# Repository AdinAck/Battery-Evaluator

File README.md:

# Battery-Evaluator
A comprehensive battery evaluator board for running simple tests and measurements, or creating a battery profile for accurately predicting charge level from voltage.

## Electrical Characteristics
- 0-5v battery (single cell)
- 0-1000mA programable constant current draw
- Do not reverse polarity of battery, the board will die
- While you *can* plug in a battery before USB is plugged in... you shouldn't

## Software Features
- Graph the measured and predicted battery voltage with respect to mAh consumed
- Measure ESR
- Measure mWh consumed
- Monitor temperature of FETs and resistors

## To Be Implemented
- More battery chemistries
- [Op-Amp oscillation fix](https://github.com/AdinAck/Battery-Evaluator/issues/1)
- Combine multiple constant current tests to make the ultimate battery profile
- Generate voltage, current -> percent charge function

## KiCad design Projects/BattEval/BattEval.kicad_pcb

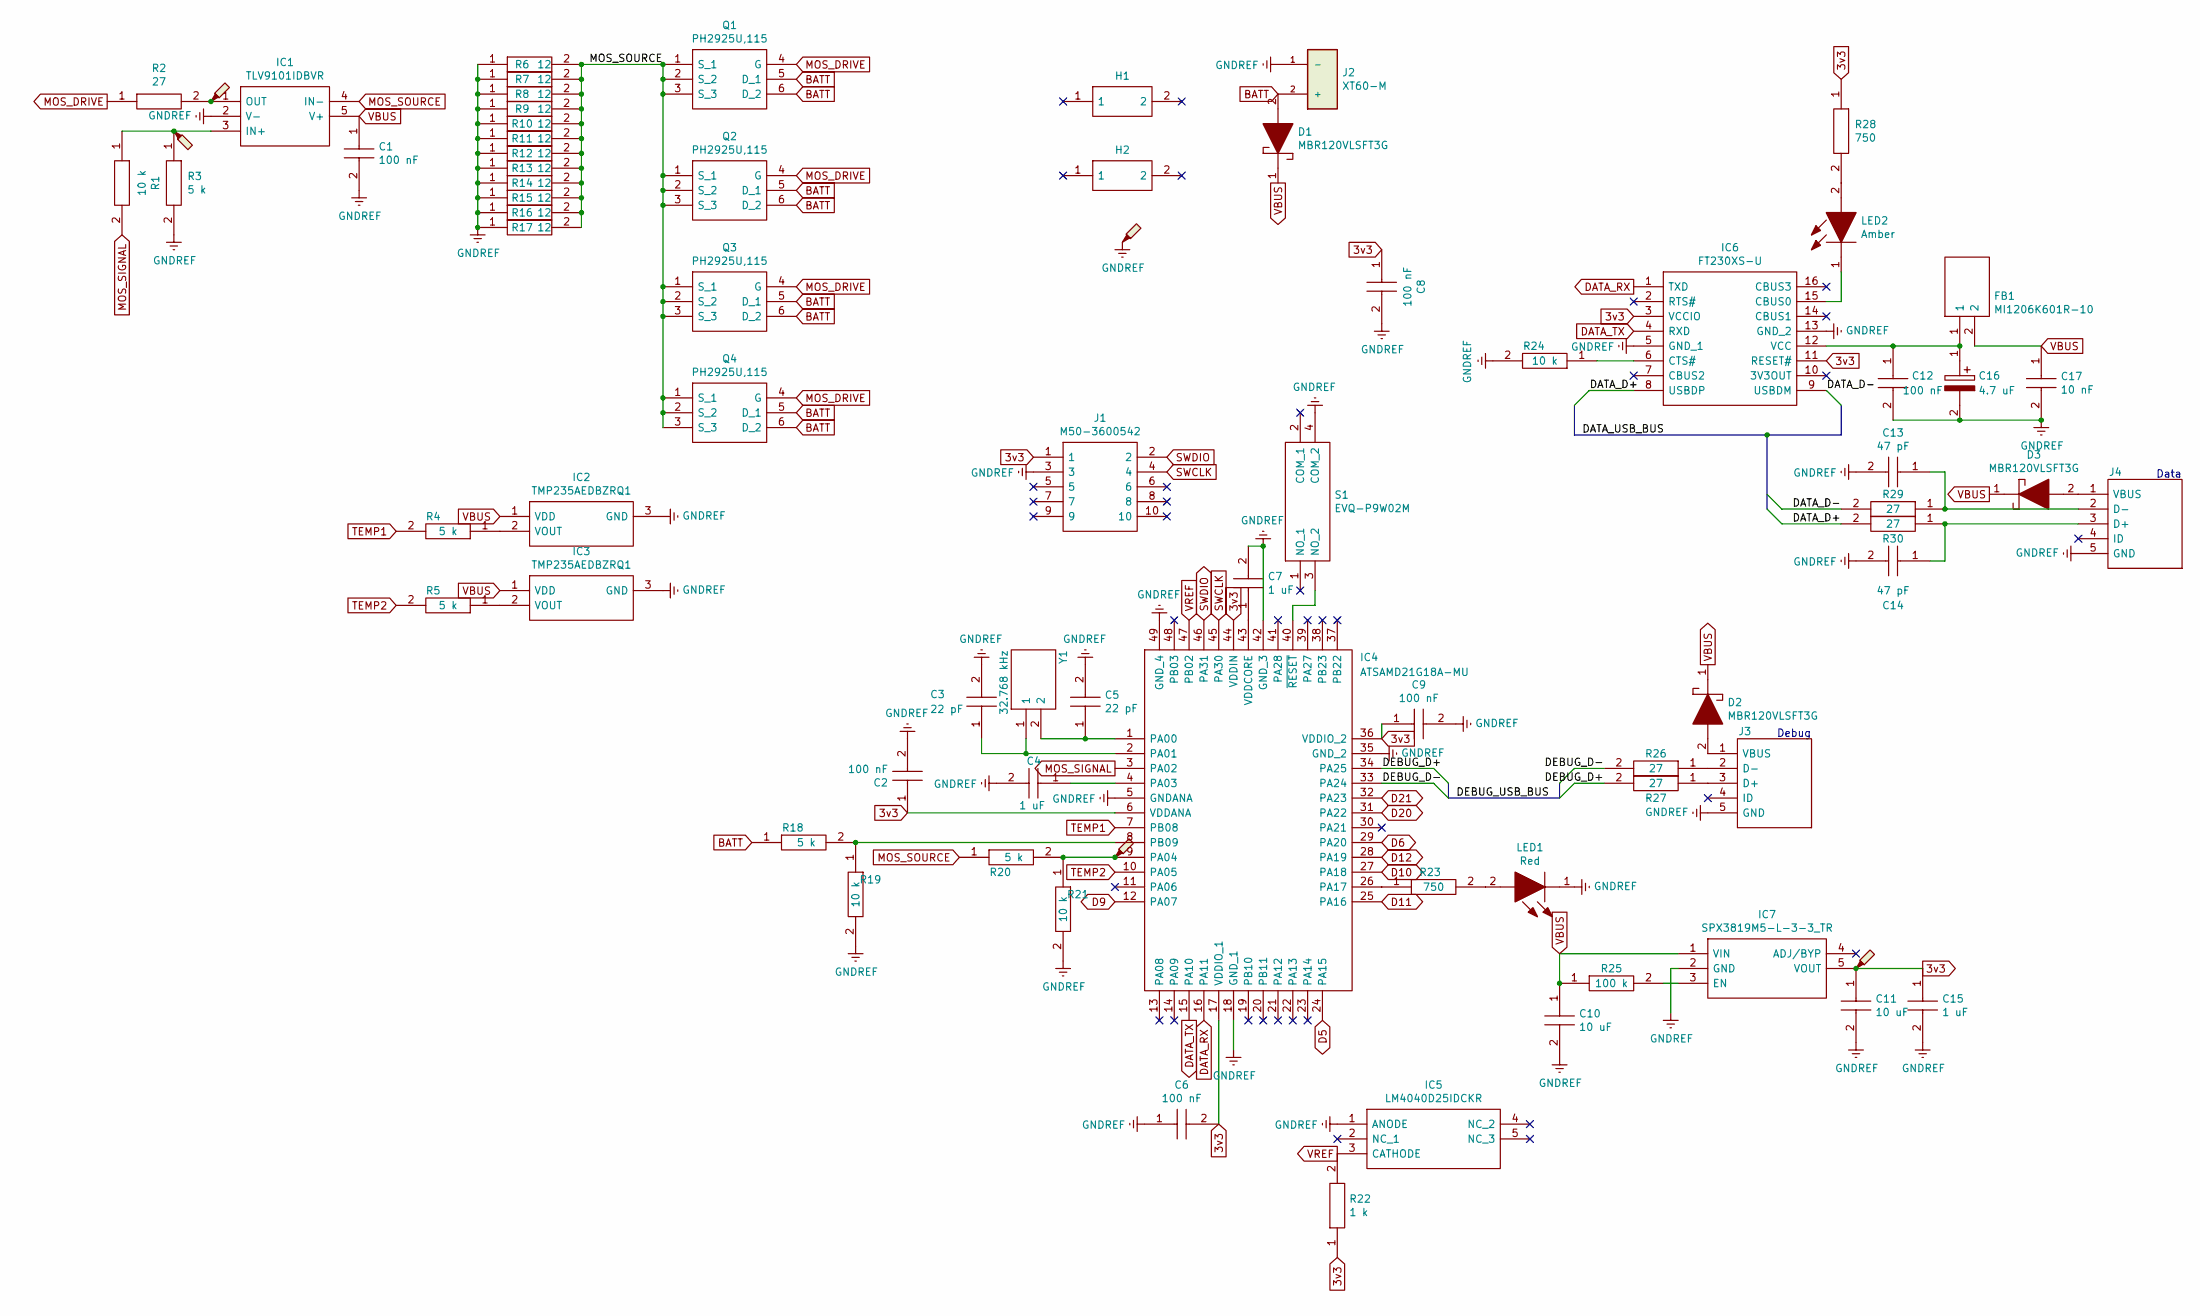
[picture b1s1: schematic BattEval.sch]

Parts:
C1, C2, C6, C8, C9, C12: 06033C104KAT2A; CAPC1608X90N; Mouser Part Number 581-06033C104KAT2A
C3, C5: 06035A220JAT4A; CAPC1608X90N; Mouser Part Number 581-06035A220JAT4A
C4, C7, C15: 0603ZC105KAT2A; CAPC1608X90N; Mouser Part Number 581-0603ZC105KAT2A
C10, C11: 0603ZD106KAT4A; CAPC1608X90N; Mouser Part Number 581-0603ZD106KAT4A
C13, C14: 06033C470KAT2A; CAPC1608X90N; Mouser Part Number 581-06033C470KAT2A
C16: TAJA475K010RNJV; CAPPM3216X180N; Mouser Part Number 581-TAJA475K010RNJV
C17: 0603ZC103KAT2A; CAPC1608X90N; Mouser Part Number 581-0603ZC103K
D1, D2, D3: MBR120VLSFT3G; SODFL3616X98N; Mouser Part Number 863-MBR120VLSFT3G
FB1: MI1206K601R-10; BEADC3216X130N; Mouser Part Number N/A
H1, H2: 960-23-12-D-AB-0; 9602312DAB0; Mouser Part Number 567-960-23-12-D-AB-0
IC1: TLV9101IDBVR; SOT95P280X145-5N; Mouser Part Number 595-TLV9101IDBVR
IC2, IC3: TMP235AEDBZRQ1; SOT95P237X112-3N; Mouser Part Number 595-TMP235AEDBZRQ1
IC4: ATSAMD21G18A-MU; QFN50P700X700X90-49N-D; Mouser Part Number 556-ATSAMD21G18A-MU
IC5: LM4040D25IDCKR; SOT65P210X110-5N; Mouser Part Number 595-LM4040D25IDCKR
IC6: FT230XS-U; SOP64P599X175-16N; Mouser Part Number 895-FT230XS-U
IC7: SPX3819M5-L-3-3_TR; SOT95P280X145-5N; Mouser Part Number 701-SPX3819M5-L-33TR
J1: M50-3600542; M503600542; Mouser Part Number 855-M50-3600542
J2: XT60-M; AMASS_XT60-M; PARTREV 1.2
J3, J4: 47346-0001; Mouser Part Number 538-47346-0001
LED1: APT1608LSECK_J3-PRV; APT1608CGCK; Mouser Part Number 604-APT1608LSECKJ3RV
LED2: 150060AS75000; LEDC1608X80N; Mouser Part Number 710-150060AS75000
Q1, Q2, Q3, Q4: PH2925U,115; PSMN5R660YLX; Mouser Part Number 771-PH2925U115
R1, R19, R21, R24: ERJ-S02F1002X; RESC1005X40N; Mouser Part Number 667-ERJ-S02F1002X
R2, R26, R27, R29, R30: ERJ2RKD27R0X; RESC1005X40N; Mouser Part Number 667-ERJ-2RKD27R0X
R3, R4, R5, R18, R20: RC0402FR-075KL; RESC1005X40N; Mouser Part Number 603-RC0402FR-075KL
R6, R7, R8, R9, R10, R11, R12, R13, R14, R15, R16, R17: CRGP2512F12R; RESC6432X65N; Mouser Part Number 279-CRGP2512F12R
R22: ERJ-U02F1001X; RESC1005X40N; Mouser Part Number 667-ERJ-U02F1001X
R23, R28: ERJ-2RKF7500X; RESC1005X40N; Mouser Part Number 667-ERJ-2RKF7500X
R25: ERJ-U02F1003X; RESC1005X40N; Mouser Part Number 667-ERJ-U02F1003X
S1: EVQ-P9W02M; EVQP9W02M; Mouser Part Number 667-EVQ-P9W02M
TP1, TP2, TP3, TP4, TP5: TestPoint_Probe; Standard_Probe_Point
Y1: CM7V-T1A-32.768kHz-6pF-20PPM-TA-QC; CM7VT1A32768kHz6pF20PPMTAQC; Mouser Part Number 428-201843-MG01

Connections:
3v3: C2.1, C6.2, C8.1, C9.1, C11.1, C15.1, IC4.6 (VDDANA), IC4.17 (VDDIO_1), IC4.36 (VDDIO_2), IC4.44 (VDDIN), IC6.3 (VCCIO), IC6.11 (RESET#), IC7.5 (VOUT), J1.1, R22.1, R28.1, TP5.1
/DATA_D+: IC6.8 (USBDP), R30.2
/DATA_D-: IC6.9 (USBDM), R29.2
/DEBUG_D+: IC4.34 (PA25), R27.2
/DEBUG_D-: IC4.33 (PA24), R26.2
BATT: D1.2, J2.2 (+), Q1.5 (D_1), Q1.6 (D_2), Q2.5 (D_1), Q2.6 (D_2), Q3.5 (D_1), Q3.6 (D_2), Q4.5 (D_1), Q4.6 (D_2), R18.1
D5: IC4.24 (PA15)
D6: IC4.29 (PA20)
D9: IC4.12 (PA07)
D10: IC4.27 (PA18)
D11: IC4.25 (PA16)
D12: IC4.28 (PA19)
D20: IC4.31 (PA22)
D21: IC4.32 (PA23)
DATA_RX: IC4.16 (PA11), IC6.1 (TXD)
DATA_TX: IC4.15 (PA10), IC6.4 (RXD)
GNDREF: C1.2, C2.2, C3.2, C4.2, C5.2, C6.1, C7.2, C8.2, C9.2, C10.2, C11.2, C12.2, C13.2, C14.2, C15.2, C16.2, C17.2, IC1.2 (V-), IC2.3 (GND), IC3.3 (GND), IC4.5 (GNDANA), IC4.18 (GND_1), IC4.35 (GND_2), IC4.42 (GND_3), IC4.49 (GND_4), IC5.1 (ANODE), IC6.5 (GND_1), IC6.13 (GND_2), IC7.2 (GND), J1.3, J2.1 (-), J3.5 (GND), J4.5 (GND), LED1.1, R3.2, R6.1, R7.1, R8.1, R9.1, R10.1, R11.1, R12.1, R13.1, R14.1, R15.1, R16.1, R17.1, R19.2, R21.2, R24.2, S1.4 (COM_2), TP4.1
MOS_DRIVE: Q1.4 (G), Q2.4 (G), Q3.4 (G), Q4.4 (G), R2.1
MOS_SIGNAL: IC4.3 (PA02), R1.2
MOS_SOURCE: IC1.4 (IN-), Q1.1 (S_1), Q1.2 (S_2), Q1.3 (S_3), Q2.1 (S_1), Q2.2 (S_2), Q2.3 (S_3), Q3.1 (S_1), Q3.2 (S_2), Q3.3 (S_3), Q4.1 (S_1), Q4.2 (S_2), Q4.3 (S_3), R6.2, R7.2, R8.2, R9.2, R10.2, R11.2, R12.2, R13.2, R14.2, R15.2, R16.2, R17.2, R20.1
unnamed: C3.1, IC4.2 (PA01), Y1.1
unnamed: C4.1, IC4.4 (PA03)
unnamed: C5.1, IC4.1 (PA00), Y1.2
unnamed: C7.1, IC4.43 (VDDCORE)
unnamed: C12.1, C16.1, FB1.1, IC6.12 (VCC)
unnamed: C13.1, J4.2 (D-), R29.1
unnamed: C14.1, J4.3 (D+), R30.1
unnamed: D2.2, J3.1 (VBUS)
unnamed: D3.2, J4.1 (VBUS)
unnamed: IC1.1 (OUT), R2.2, TP2.1
unnamed: IC1.3 (IN+), R1.1, R3.1, TP1.1
unnamed: IC2.2 (VOUT), R4.1
unnamed: IC3.2 (VOUT), R5.1
unnamed: IC4.8 (PB09), R18.2, R19.1
unnamed: IC4.9 (PA04), R20.2, R21.1, TP3.1
unnamed: IC4.26 (PA17), R23.1
unnamed: IC4.40 (~RESET), S1.3 (NO_2)
unnamed: IC6.6 (CTS#), R24.1
unnamed: IC6.15 (CBUS0), LED2.1
unnamed: IC7.3 (EN), R25.2
unnamed: J3.2 (D-), R26.1
unnamed: J3.3 (D+), R27.1
unnamed: LED1.2, R23.2
unnamed: LED2.2, R28.2
SWCLK: IC4.45 (PA30), J1.4
SWDIO: IC4.46 (PA31), J1.2
TEMP1: IC4.7 (PB08), R4.2
TEMP2: IC4.10 (PA05), R5.2
VBUS: C1.1, C10.1, C17.1, D1.1, D2.1, D3.1, FB1.2, IC1.5 (V+), IC2.1 (VDD), IC3.1 (VDD), IC7.1 (VIN), R25.1
VREF: IC4.47 (PB02), IC5.3 (CATHODE), R22.2

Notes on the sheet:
Debug
Data

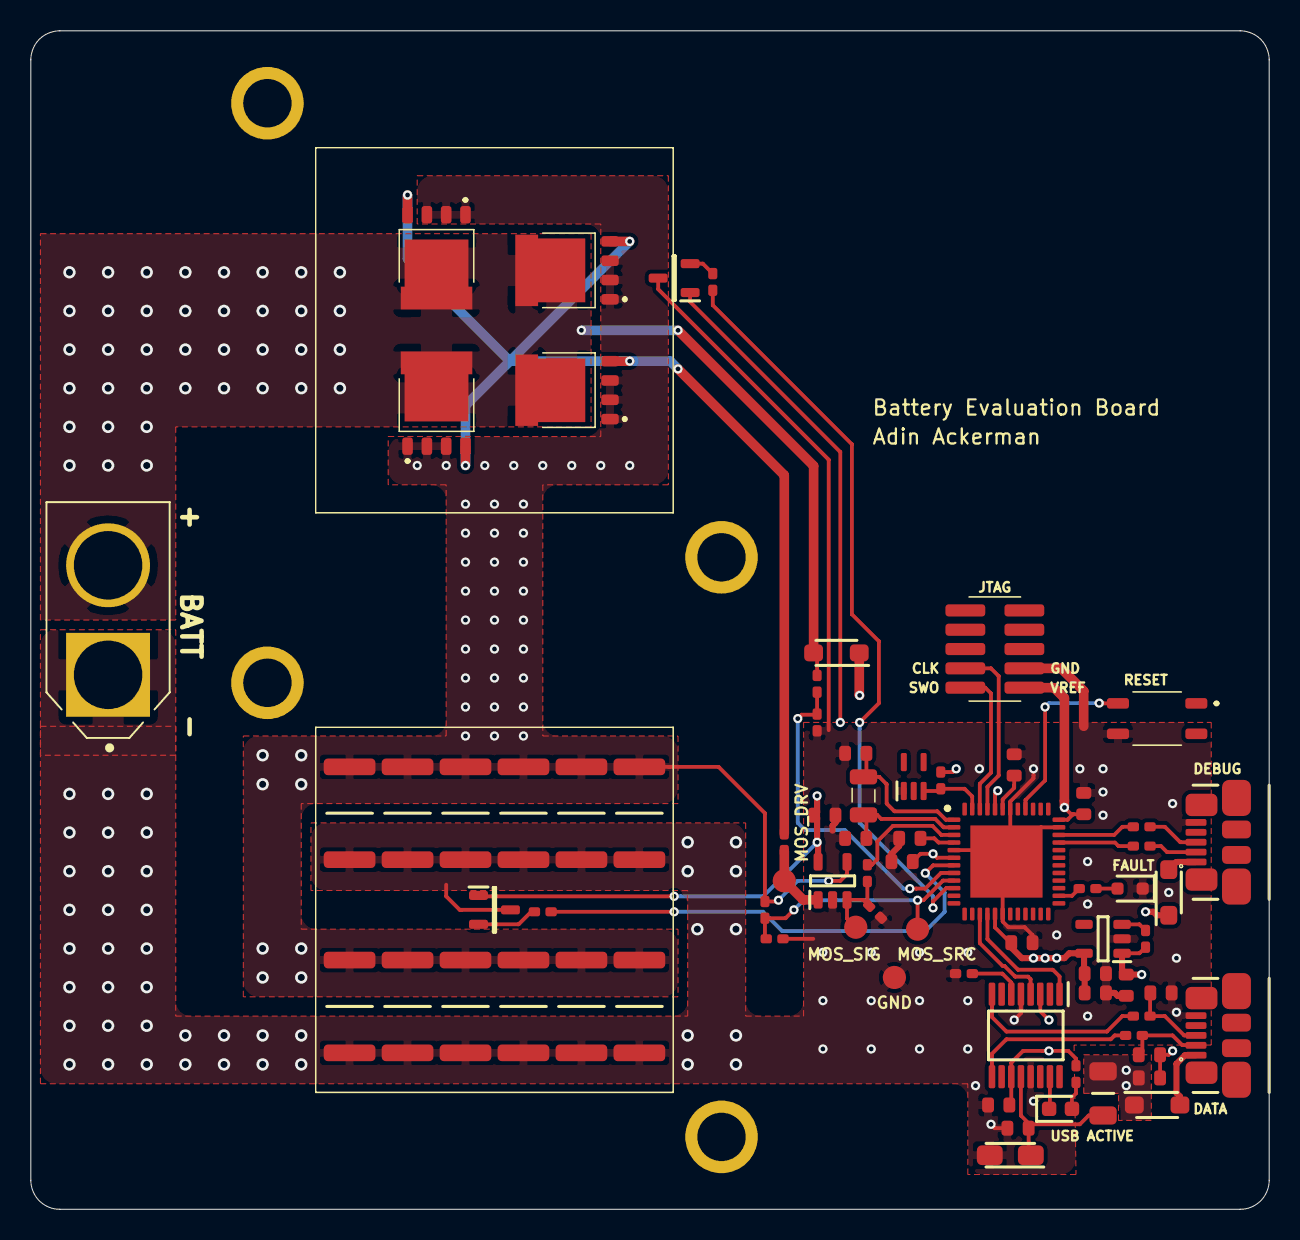
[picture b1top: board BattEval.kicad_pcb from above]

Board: 2 copper layers, 81.4 x 77.5 mm, 77 parts (1 on the bottom side), 42 nets.

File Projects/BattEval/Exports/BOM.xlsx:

Reference | Mouser Part Number | Manufacturer Name | Manufacturer Part Number | Mouser Price/Stock | Quantity
> C3, C5 | 06035A220JAT4A | AVX | 581-06035A220JAT4A | https://www.mouser.co.uk/ProductDetail/AVX/06035A220JAT4A/?q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 | 2
> C4, C7, C15 | 0603ZC105KAT2A | AVX | 581-0603ZC105KAT2A | https://www.mouser.com/Search/Refine.aspx?Keyword=581-0603ZC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 | 3
> C1, C2, C6, C8, C9, C12 | 06033C104KAT2A | AVX | 581-06033C104KAT2A | https://www.mouser.co.uk/ProductDetail/AVX/06033C104KAT2A/?q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 | 6
> C10, C11 | 0603ZD106KAT4A | AVX | 581-0603ZD106KAT4A | https://www.mouser.co.uk/ProductDetail/AVX/0603ZD106KAT4A?qs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 | 2
> C13, C14 | 06033C470KAT2A | AVX | 581-06033C470KAT2A | http://www.mouser.com/Search/ProductDetail.aspx?qs=zRMn1EiLH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 | 2
C16 | TAJA475K010RNJV | AVX | 581-TAJA475K010RNJV | https://www.mouser.co.uk/ProductDetail/AVX/TAJA475K010RNJV?q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 | 1
C17 | 0603ZC103KAT2A | AVX | 581-0603ZC103K | https://www.mouser.com/Search/Refine.aspx?Keyword=581-0603ZC103K | 1
> D1-D3 | MBR120VLSFT3G | ON Semiconductor | 863-MBR120VLSFT3G | https://www.mouser.co.uk/ProductDetail/ON-Semiconductor/MBR1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 | 3
FB1 | MI1206K601R-10 | Laird Technologies | N/A | https://www.mouser.com/Search/Refine.aspx?Keyword=N%2FA | 1
> H1, H2 | 960-23-12-D-AB-0 | Wakefield-Vette | 567-960-23-12-D-AB-0 | https://www.mouser.co.uk/ProductDetail/Wakefield-Vette/960-2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 | 2
IC1 | TLV9101IDBVR | Texas Instruments | 595-TLV9101IDBVR | https://www.mouser.co.uk/ProductDetail/Texas-Instruments/TLV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 | 1
> IC2, IC3 | TMP235AEDBZRQ1 | Texas Instruments | 595-TMP235AEDBZRQ1 | https://www.mouser.co.uk/ProductDetail/Texas-Instruments/TMP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 | 2
IC4 | ATSAMD21G18A-MU | Microchip | 556-ATSAMD21G18A-MU | https://www.mouser.co.uk/ProductDetail/Microchip-Technology/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 | 1
IC5 | LM4040D25IDCKR | Texas Instruments | 595-LM4040D25IDCKR | https://www.mouser.co.uk/ProductDetail/Texas-Instruments/LM4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 | 1
IC6 | FT230XS-U | FTDI Chip | 895-FT230XS-U | https://www.mouser.co.uk/ProductDetail/FTDI/FT230XS-U/?qs=Gp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 | 1
IC7 | SPX3819M5-L-3-3_TR | MaxLinear, Inc. | 701-SPX3819M5-L-33TR | https://www.mouser.co.uk/ProductDetail/MaxLinear/SPX3819M5-L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 | 1
J1 | M50-3600542 | Harwin | 855-M50-3600542 | https://www.mouser.co.uk/ProductDetail/Harwin/M50-3600542/?q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 | 1
J2 | XT60-M |  |  |  | 1
> J3, J4 | 47346-0001 | Molex | 538-47346-0001 | https://www.mouser.co.uk/ProductDetail/Molex/47346-0001/?qs=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 | 2
LED1 | APT1608LSECK_J3-PRV | Kingbright | 604-APT1608LSECKJ3RV | https://www.mouser.co.uk/ProductDetail/Kingbright/APT1608LSE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 | 1
LED2 | 150060AS75000 | Wurth Elektronik | 710-150060AS75000 | https://www.mouser.co.uk/ProductDetail/Wurth-Elektronik/1500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 | 1
> Q1-Q4 | PH2925U,115 | Nexperia | 771-PH2925U115 | https://www.mouser.co.uk/ProductDetail/Nexperia/PH2925U115?q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 | 4
> R1, R17, R19, R22 | ERJ-S02F1002X | Panasonic | 667-ERJ-S02F1002X | https://www.mouser.co.uk/ProductDetail/Panasonic/ERJ-S02F100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 | 4
> R3, R16, R18 | RC0402FR-075KL | YAGEO (PHYCOMP) | 603-RC0402FR-075KL | https://www.mouser.co.uk/ProductDetail/Yageo/RC0402FR-075KL/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 | 3
> R4-R15 | CRGP2512F12R | TE Connectivity | 279-CRGP2512F12R | https://www.mouser.co.uk/ProductDetail/TE-Connectivity-Holsw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 | 12
R20 | ERJ-U02F1001X | Panasonic | 667-ERJ-U02F1001X | https://www.mouser.com/Search/Refine.aspx?Keyword=667-ERJ-U02F1001X | 1
> R21, R26 | ERJ-2RKF7500X | Panasonic | 667-ERJ-2RKF7500X | https://www.mouser.com/Search/Refine.aspx?Keyword=667-ERJ-2RKF7500X | 2
R23 | ERJ-U02F1003X | Panasonic | 667-ERJ-U02F1003X | https://www.mouser.com/Search/Refine.aspx?Keyword=667-ERJ-U02F1003X | 1
> R2, R24, R25, R27, R28 | ERJ2RKD27R0X | Panasonic | 667-ERJ-2RKD27R0X | https://www.mouser.com/Search/Refine.aspx?Keyword=667-ERJ-2RKD27R0X | 5
S1 | EVQ-P9W02M | Panasonic | 667-EVQ-P9W02M | https://www.mouser.co.uk/ProductDetail/Panasonic/EVQ-P9W02M?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 | 1
> TP1-TP5 | TestPoint_Probe |  |  |  | 5
Y1 | CM7V-T1A-32.768kHz-6pF-20PPM-TA-QC | Micro Crystal AG | 428-201843-MG01 | https://www.mouser.co.uk/ProductDetail/Micro-Crystal/CM7V-T1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 | 1

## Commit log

2021-05-16 first
2021-05-16 removed unused import
2021-05-18 added code on board
2021-06-02 first implementation of constant power draw mode
2021-07-13 better graphs, fixed freezing on mouse event
2021-07-14 test would run forever, fixed
2021-07-14 thermal throttling!
2021-07-15 so many things, better ESR stuff, configuration stuff, more buttons, etc
2021-07-15 separated gui updates from io updates to hopefully prevent OS from sleeping the program
2021-07-17 all is good, problems were from non-native python environment
2021-07-18 ESR measurement is faster, fixed unresolved current after error, improved feedback speed
2021-07-18 human readable device selector, ESR is super fast and consistent
2021-07-18 automatically detects and connects to board, squashed some bugs
2021-07-18 why was watchdog imported???
